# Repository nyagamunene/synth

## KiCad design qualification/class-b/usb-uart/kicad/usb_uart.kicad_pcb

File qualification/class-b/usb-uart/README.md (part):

# USB-C dual UART + RS-485 adapter (SYN-66)

Status: design, placement and a FreeRouting route that passes Synth's release gate. The routed PCB, KiCad project and reports are in this PR. Not fabricated, not tested on hardware.
Do not call it proven or clean. The list of what is unchecked is at the bottom.

Intended use: bench or lab adapter, short cables, point-to-point or last node on an RS-485 bus. Not for industrial installs, long cable runs or a node in the middle of a multidrop bus: A and B have no surge protection beyond the transceiver's built-in ESD, and the 120 ohm termination is always connected. The surge parts and a selectable termination are a later revision; the registry parts for them are in #356.

## What it is

- One USB-C port, one WCH CH342F (two UARTs).
- UART1 goes to pin headers as TTL (J2: GND, TXD1, RXD1; J3: DTR1, RTS1, CTS1).
- UART0 drives a TI THVD1450D RS-485 transceiver. Header J4: A, B, GND.
- DTR0/TNOW0 switches the transceiver direction. R_TNOW (4.7k to GND) puts UART0 in the CH342 half-duplex mode.
- Protection: PRTR5V0U2X on D+/D-, PTVS6V0S1UR on VBUS, CC1 and CC2. A 3.3 V LDO (LP5907) feeds the +3V3 rail.
- Four M2.5 mounting holes (H1 to H4), pinned in the placement sidecar: two at the top corners, two on the left and right edges at mid-height. The bottom corners are taken by the header row. Screw size and standoff height are not chosen.
- Source: `usb_uart.synth`. Sidecar: `usb_uart.placement.layout.toml` (board mm). The schematic has no sidecar: the compiler lays it out, one region per group.

## VIO jumper (J_VIO)

VIO is the I/O rail of both UARTs, the reset pin and the RS-485 chip. It is always 3.3 V or 5 V.
The THVD1450 needs 3 V or more, so 1.8 V and target-powered VIO were dropped.

| Jumper | VIO | Notes |
| --- | --- | --- |
| pins 1-2 | 3.3 V (LP5907) | default choice |
| pins 2-3 | 5 V (VBUS) | |
| none | off | CH342F stays in reset (VIO under 0.8 to 1.15 V), no enumeration. VIO LED is off. |

- VIO is not on J2 or J3, so a target cannot back-feed it. Do not wire anything to J_VIO pin 2.
- Forgotten jumper: the board only looks dead, and the VIO LED shows it.
- Not harmless with a powered target: a target driving RXD1 or CTS1 with VIO off goes past the CH342F limit of VIO+0.5 V.
  R5 and R6 (1k) limit the current to about 2.6 mA (3.3 V target) or 4.3 mA (5 V). The datasheet gives no clamp rating. Add the jumper first.

## Unused CH342F pins

- RI0, RI1, DCD0, DCD1, DSR0, DSR1: R8 (10k) pulls them to VIO (inactive, active low).
- CTS0: R9 (10k) holds it low, so UART0 flow control cannot stall.
- RST: left open (internal pull-up). The datasheet says unused lines may be left open; they are tied anyway.
- CTS1 floats if J3 is unplugged. Datasheet gives no pull-up for it.
- Datasheet 5.3: a pull-down on DTR1 at power-on switches UART1 to half-duplex. A target that holds DTR1 low at power-up changes the mode.

## BOM

| Ref | Part | MPN | Datasheet (revision seen) |
| --- | --- | --- | --- |
| U1 | WCH USB dual UART | CH342F | https://www.wch-ic.com/downloads/CH342DS1_PDF.html, V1E (file id 295, dated 2022-01-27) |
| U3 | TI RS-485 transceiver | THVD1450D | https://www.ti.com/lit/ds/symlink/thvd1450.pdf, SLLSEY3E (May 2018, rev May 2019) |
| U2 | TI 3.3 V LDO | LP5907MFX-3.3 | https://www.ti.com/lit/ds/symlink/lp5907.pdf, SNVS798Q (rev Jul 2025) |
| D1 | Nexperia USB ESD | PRTR5V0U2X | https://assets.nexperia.com/documents/data-sheet/PRTR5V0U2X.pdf, dated 1 Apr 2023 |
| D2, D5, D6 | Nexperia TVS 6 V | PTVS6V0S1UR | https://assets.nexperia.com/documents/data-sheet/PTVSXS1UR_SER.pdf, dated 1 Dec 2025 |
| D3 | Lite-On green LED | LTST-C190KGKT | https://optoelectronics.liteon.com/upload/download/DS22-2000-074/LTST-C190KGKT.PDF, revision not checked (site not reachable) |
| D4, D7 | Lite-On red LED | LTST-C190KRKT | https://optoelectronics.liteon.com/upload/download/DS-22-99-0151/LTST-C190KRKT.PDF, revision not checked (site not reachable) |
| J1 | USB-C receptacle | TYPE-C-31-M-12 | none in the registry, not checked |
| J2, J3, J4, J_VIO | 2.54 mm headers | generic 1x3 | none |
| C2, C3 | 2.2 uF X7R 0603 | generic | none |
| C4, C5, C6, C7 | 100 nF X7R 0603 | generic | none |
| R1, R2 | 5.1k | generic | none |
| R3, R4, R7 | 470 | generic | none |
| R5, R6 | 1k | generic | none |
| R8, R9 | 10k | generic | none |
| R_TNOW | 4.7k 1% | generic | none |
| R_TERM | 120 ohm 1% | generic | none |

Checked by me against the manufacturer file in this work: CH342F, THVD1450D, LP5907 (revision line only), the two Nexperia parts (revision line only).
The Nexperia and LP5907 electrical numbers were not re-read.

## Placement and routing (this commit)

Status: compact placement done and routed with FreeRouting. The route passes Synth's release gate; it is not reviewed or fabricated.

- Two copper layers: signals on F.Cu and B.Cu, a GND pour on both. The route uses no inner layer because the board has none; the previous revision was four layers with two inner GND planes that carried no routing.
- Outline: 40.99 x 32.23 mm as routed. The four M2.5 holes are at x 5.5 and 39.6 mm, y 3.0 and 21.0 mm, with a 2.2 mm board-feature rim. The header courtyards at y 29.9 mm set the 32.23 mm height. This is 3.5 mm shorter than the previous 35.73 mm compact layout and 7.5 mm shorter than the 39.73 mm committed board.
- Board-feature rim: Synth gives a mounting hole, test point or fiducial a fixed 2.2 mm rim in the fitted outline. With this sidecar the rim does not decide the outline: the holes are not the outermost parts, and the export gives the same outline with the rim set to 0. It matters if a hole is moved to the edge, where the tight 1.5 mm fit would otherwise cut it and split the F.Cu GND pour. `tests/usb_uart_board.rs` checks that every hole keeps at least 1.5 mm of room to Edge.Cuts on the exported board. The exporter sets `island_removal_mode 0`, dropping copper islands that touch no pad. KiCad lists a GND zone against itself when two fill islands that reach pads are not joined; Synth's gate now blocks on that. The previous revision had exactly this split.
- Every part has a position in `usb_uart.placement.layout.toml`. J1 sits flush on the top edge. J_VIO, J2, J3 and J4 sit at y 29.9 mm. J_VIO, J2, J3 and J4 are at x 7.36, 16.46, 26.0 and 35.1 mm. J3 and J4 each moved 1 mm left of their previous 27.0 and 36.1 mm: at the previous spot the GND pour split into two islands (C4 pin 2, J2 pin 1, D3 pin 1 and one via were cut off) and, with current KiCad and FreeRouting here, DTR1 was left unrouted. The 9.1 mm spacing between J3 and J4 keeps their 8.62 mm courtyards apart. The bottom parts sit at y 23.6 and 25.8 mm. R1 and R2 use the top corners; R3 moved to x 14.5 mm to clear H3.
- No courtyard overlaps. J1 courtyard to top edge: 0.01 mm. That is the 0.5 mm courtyard margin reaching the edge: the shell front face sits 0.50 mm inside Edge.Cuts. The HRO drawing states no overhang limit, so only the enclosure cutout fit is left to check.
- Pad-edge gap to the target pad on the same net:

| Part | Target | Gap mm |
| --- | --- | --- |
| C4 (VDD5) | U1 pin 7 | 0.97 |
| C5 (V3) | U1 pin 6 | 1.14 |
| C6 (VIO) | U1 pin 5 | 0.99 |
| C7 (VCC) | U3 pin 8 | 0.99 |
| C2 (LDO in) | U2 VBUS pins | 0.99 |
| C3 (LDO out) | U2 pin 5 | 0.99 |
| D1 D+ / D- | J1 D+ / D- pads | 1.76 / 1.69 |
| D2 (VBUS TVS) | J1 VBUS pad | 2.34 |
| D5 (CC1 TVS) | J1 CC1 pad | 1.95 |
| D6 (CC2 TVS) | J1 CC2 pad | 1.60 |

- D2 is over 2 mm: four protection parts do not fit side by side under the 7 mm of J1 pads any closer.
- R1 and R2 are in the top corners; the remaining passives are placed by hand. The DRC checks their courtyards, not placement quality.

Routing (FreeRouting 2.4.1, `router: "freerouting"`, `allow_via_in_pad: true`), with the Synth sources at `08b917b` (`source_revision` in `reports/release.json`):
- Result: routed. `release.json` has `release_ready` true and `routing.state` "routed", with no open net. `kicad-cli pcb drc --severity-all --refill-zones`: 0 errors, 0 warnings and no `unconnected_items`. Synth's gate no longer accepts a GND zone that KiCad lists against itself, and the delivered board has none. pcbnew's connectivity puts every GND pad and via in one cluster, so the pour is connected. (The earlier revision's 36 library-link warnings came from a run without the KiCad libraries.)
- 273 track segments, 43 vias, 515.4 mm of copper.
- The routed board is 40.99 x 32.23 mm.
- FreeRouting's escape analysis flags J1 and U1 (0.5 mm pitch) as the packages where neither a fabrication-floor via nor a minimum track fits between adjacent pads, and suggests 4 layers. The route still completes, with its only via-in-pad at U1 pin 25.
- J3 is at x 26.0 mm and J4 at x 35.1 mm in the sidecar. Small placement changes change FreeRouting's result: shifts of 0.5 mm in J3 and J4 left DTR1, TNOW0 or +3V3 unrouted, and a 0.5 mm shift of C4 left USB_DN open. The same inputs gave the same board on three runs.
- Via-in-pad at the U1 exposed pad (pin 25), at (23.900, 17.300) mm. The fab must fill and cap it. JLCPCB has not been asked.
- Signal-integrity pass: 23 warnings, none blocking. All 23 are layer changes with no ground return via within 1.53 mm, so the return current has to jump between the F.Cu and B.Cu pours.
- The USB pair is not coupled. Measured on the committed board: full-speed part, pair on F.Cu only with no via (the 23 layer-change warnings are on other nets), DP 38.63 mm and DN 13.52 mm so 25.11 mm of skew (about 0.2 percent of a full-speed bit), and 91.4 percent of the length over solid B.Cu GND fill. These are my measurements, not an independent review; see `qualification.json`. FreeRouting does not couple the pair. On two layers at 1.6 mm, a 90 ohm differential pair needs about 1.18 mm traces, so the pair has no impedance target and no controlled-impedance geometry (the previous four-layer revision declared 90 ohm but never verified it).
- No part has been reviewed (`reviewer_state` is false for every part in `release.json`).
- Silkscreen: the D7, J4, J_VIO and U1 reference labels are placed by hand in the sidecar. `kicad-cli pcb drc` reports no silkscreen warning.
- TX LEDs: D4 and D7 take their current from VIO through R4 and R7 and sink it into TXD0 and TXD1, so they are dark while a line idles and lit on the low bits. Each draws about 3 mA at 3.3 V and 6.6 mA at 5 V from the CH342 TXD pin (an estimate from a 1.9 V forward drop; the CH342 output drive was not checked at 5 V).

## Committed artifacts

- `kicad/`: the routed PCB, schematic, symbol library, project, DRC rules and BOM.
- `reports/`: `release.json`, the delivered DRC, ERC and the routing record. Its `production_status` and `release_ready` fields only mean the route passed Synth's router and DRC gates, and its `gate_scope` field says so. Neither is a fabrication approval.
- `qualification.json`: the qualification gate. `qualified` stays false until every review gate in it is true.
- `dfm/`: the gerber zip, CPL and screenshots from the JLCPCB quote and DFM flow on 2026-10-27 (no order placed). It is partial: see `jlcpcb_dfm` in `qualification.json`.
- `images/`: 3D top and angled, top and bottom copper, and the schematic. The 3D and copper pictures were rendered with `kicad-cli pcb render` and `pcb export pdf` from the committed board.
- `dfm/`: regenerated Gerbers, drill and CPL for this board. The JLCPCB screenshots there are from the previous revision and were not redone; see `qualification.json`.
- `SHA256SUMS`: hashes of the artifacts above.

The reports are as the commands produce them, except that the absolute paths of the machine that produced them were cut to repo-relative ones (`out/...` is the export directory) and `source_revision` in `reports/release.json` was added by hand. The release report is the CLI's own format (`synth.release.v1`), which differs from the MCP report in the earlier revision.

The committed board came from the CLI commands below (FreeRouting engine, via-in-pad allowed).

## Commands (use an empty `XDG_DATA_HOME` so a user registry cannot shadow parts)

```
export XDG_DATA_HOME=$(mktemp -d)
scripts/setup-routing-engines.sh --freerouting-only
synth validate qualification/class-b/usb-uart/usb_uart.synth
synth export-kicad qualification/class-b/usb-uart/usb_uart.synth --out /tmp/usb_uart --router free-routing --krt-allow-via-in-pad
kicad-cli pcb drc --severity-all --refill-zones --format json /tmp/usb_uart/usb_uart.kicad_pcb -o /tmp/usb_uart/usb_uart-drc.json
kicad-cli sch erc --severity-all --format json /tmp/usb_uart/usb_uart.kicad_sch -o /tmp/usb_uart/usb_uart-erc.json
(cd qualification/class-b/usb-uart && sha256sum -c SHA256SUMS)
```

A route that passes the gate is `usb_uart.kicad_pcb`; a failed one stays in `usb_uart.freerouting.kicad_pcb`. The unrouted placement is `usb_uart.synth.kicad_pcb`.
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
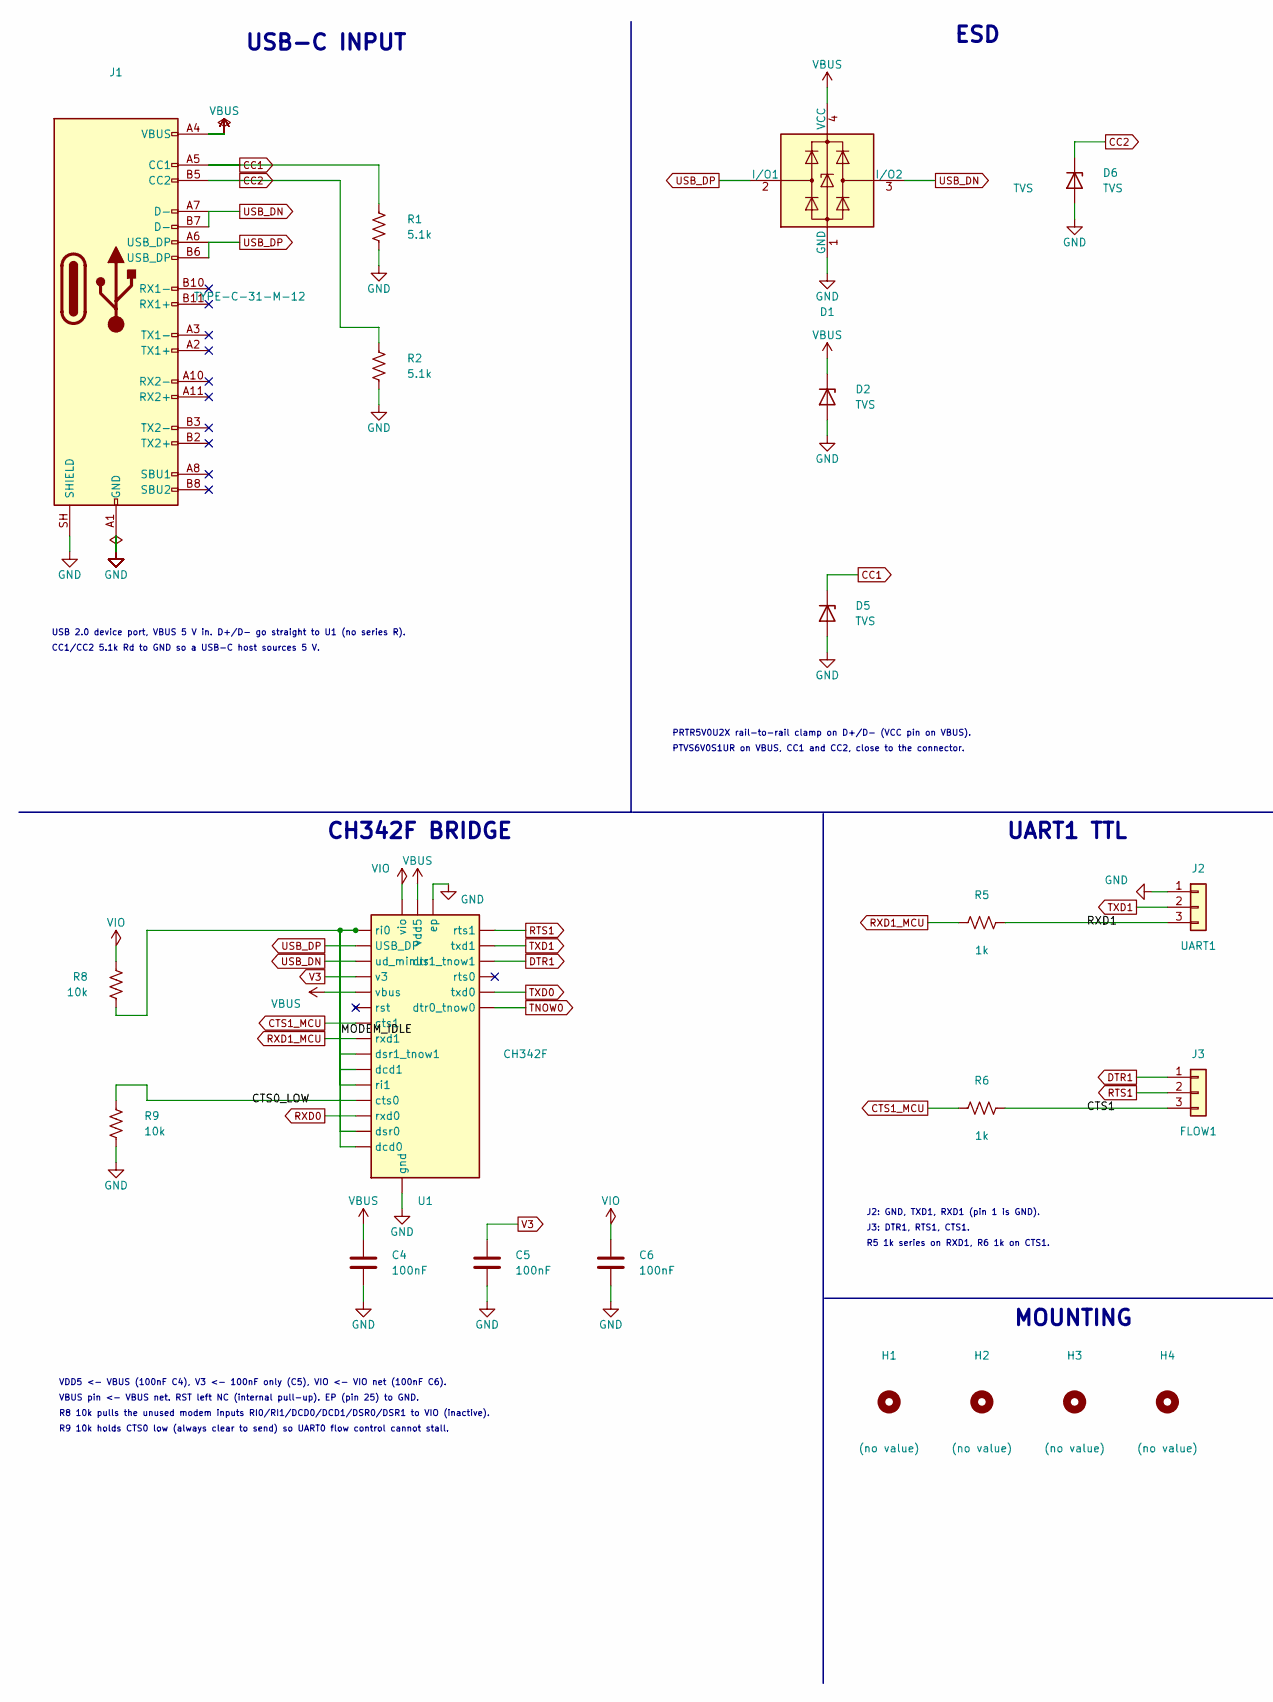
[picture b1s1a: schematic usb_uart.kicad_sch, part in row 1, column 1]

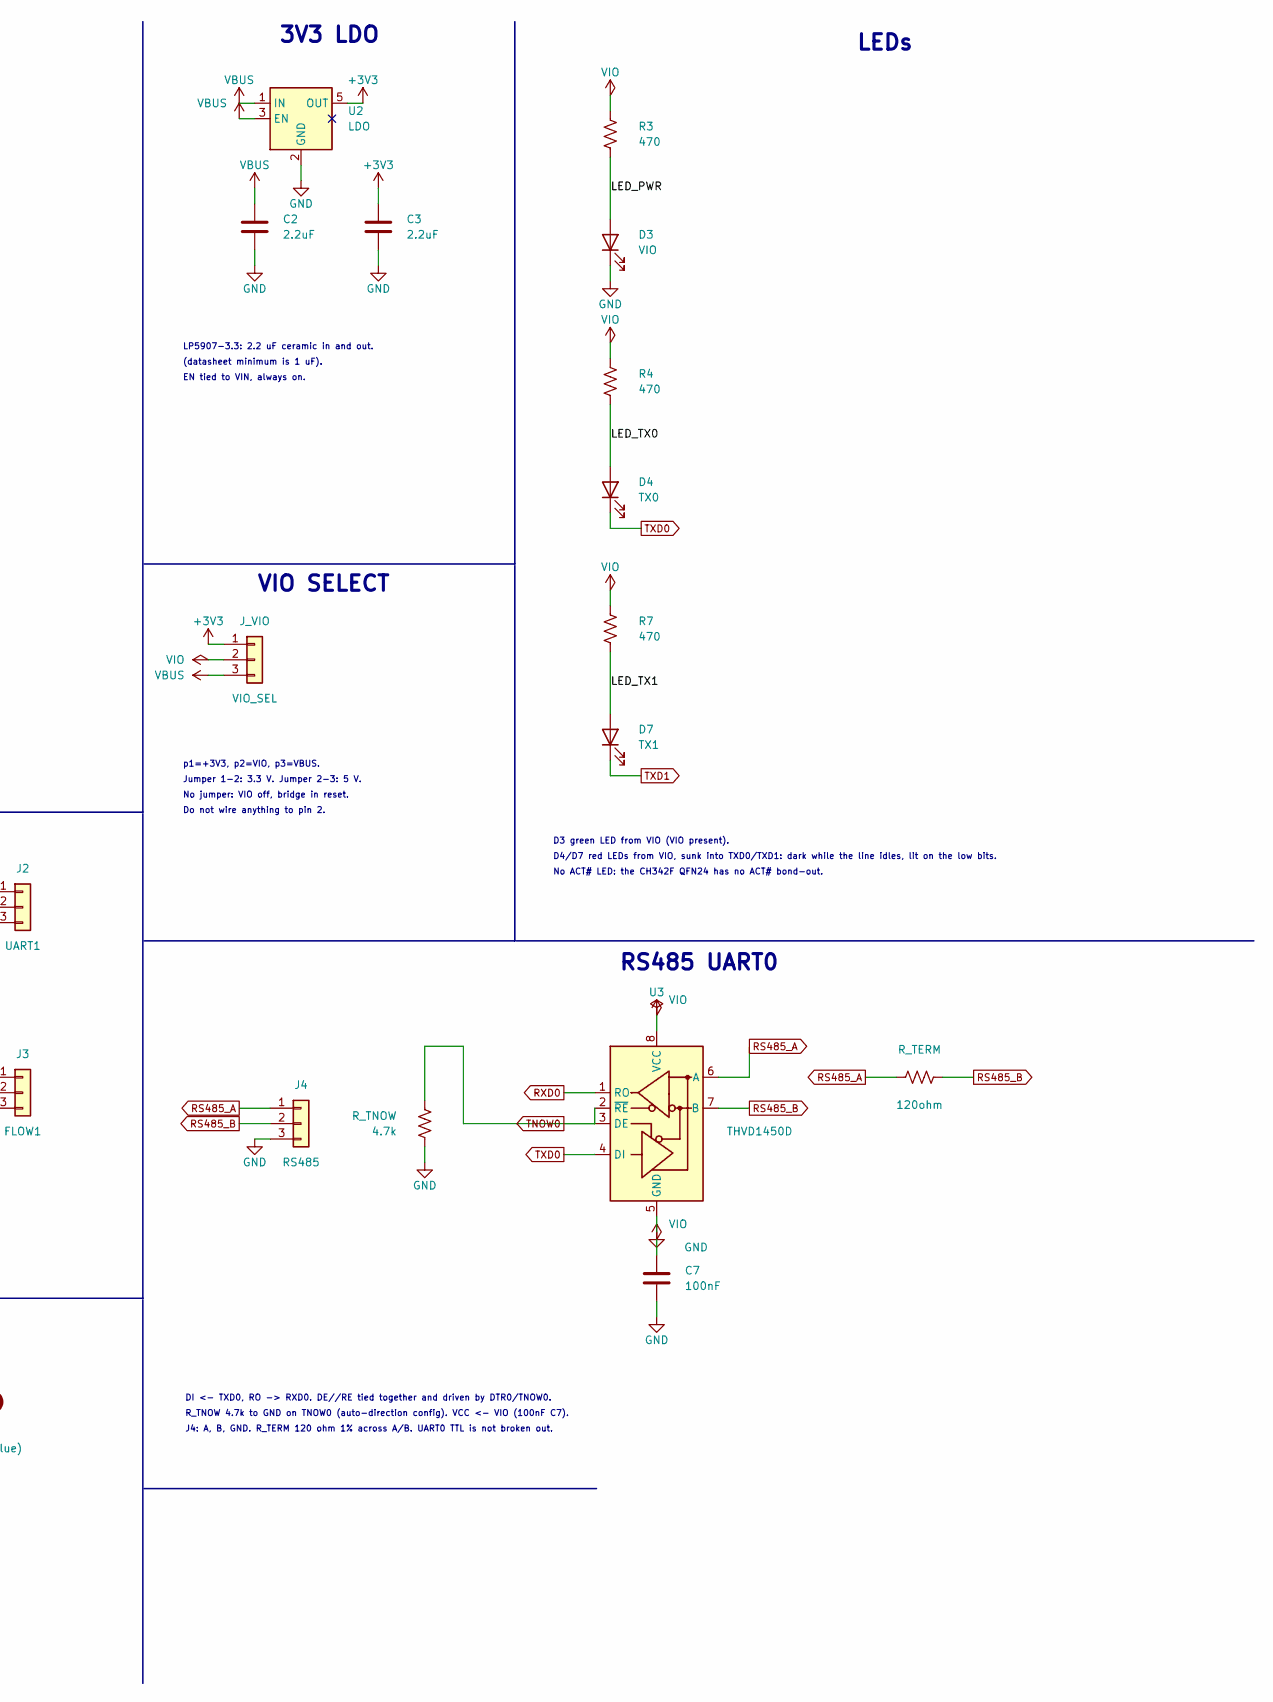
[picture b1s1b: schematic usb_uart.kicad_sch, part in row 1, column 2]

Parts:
C2, C3: 2.2uF; C_0603_1608Metric; Voltage 16V
C4, C5, C6, C7: 100nF; C_0603_1608Metric; Voltage 16V
D1: TVS; SOT-143; MPN PRTR5V0U2X
D2, D5, D6: TVS; Nexperia_CFP3_SOD-123W; MPN PTVS6V0S1UR
D3: VIO; LED_0603_1608Metric; MPN LTST-C190KGKT
D4: TX0; LED_0603_1608Metric; MPN LTST-C190KRKT
D7: TX1; LED_0603_1608Metric; MPN LTST-C190KRKT
H1, H2, H3, H4: (no value); MountingHole_2.5mm
J1: TYPE-C-31-M-12; USB_C_Receptacle_HRO_TYPE-C-31-M-12; MPN TYPE-C-31-M-12; LCSC C165948
J2: UART1; PinHeader_1x03_P2.54mm_Vertical
J3: FLOW1; PinHeader_1x03_P2.54mm_Vertical
J4: RS485; PinHeader_1x03_P2.54mm_Vertical
J_VIO: VIO_SEL; PinHeader_1x03_P2.54mm_Vertical
R1, R2: 5.1k; R_0603_1608Metric
R3, R4, R7: 470; R_0603_1608Metric
R5, R6: 1k; R_0603_1608Metric
R8, R9: 10k; R_0603_1608Metric
R_TERM: 120ohm; R_0603_1608Metric; Tolerance 1%
R_TNOW: 4.7k; R_0603_1608Metric; Tolerance 1%
U1: CH342F; QFN-24-1EP_4x4mm_P0.5mm_EP2.6x2.6mm; MPN CH342F; LCSC C2841530
U2: LDO; SOT-23-5; MPN LP5907MFX-3.3; LCSC C83437
U3: THVD1450D; SOIC-8_3.9x4.9mm_P1.27mm; MPN THVD1450D; LCSC C2671361

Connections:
+3V3: C3.1, J_VIO.1, U2.5 (OUT)
CC1: D5.1 (K), J1.A5 (CC1), R1.1
CC2: D6.1 (K), J1.B5 (CC2), R2.1
CTS0_LOW: R9.1, U1.18 (cts0)
CTS1: J3.3, R6.2
CTS1_MCU: R6.1, U1.10 (cts1)
DTR1: J3.1, U1.15 (dtr1_tnow1)
GND: C2.2, C3.2, C4.2, C5.2, C6.2, C7.2, D1.1 (GND), D2.2 (A), D3.1 (K), D5.2 (A), D6.2 (A), J1.A1 (GND), J1.A12 (GND), J1.B1 (GND), J1.B12 (GND), J1.SH (SHIELD), J2.1, J4.3, R1.2, R2.2, R9.2, R_TNOW.2, U1.2 (gnd), U1.25 (ep), U2.2 (GND), U3.5 (GND)
LED_PWR: D3.2 (A), R3.2
LED_TX0: D4.2 (A), R4.2
LED_TX1: D7.2 (A), R7.2
MODEM_IDLE: R8.2, U1.1 (ri0), U1.14 (dsr1_tnow1), U1.16 (dcd1), U1.17 (ri1), U1.22 (dsr0), U1.24 (dcd0)
RS485_A: J4.1, R_TERM.1, U3.6 (A)
RS485_B: J4.2, R_TERM.2, U3.7 (B)
RTS1: J3.2, U1.11 (rts1)
RXD0: U1.20 (rxd0), U3.1 (RO)
RXD1: J2.3, R5.2
RXD1_MCU: R5.1, U1.12 (rxd1)
TNOW0: R_TNOW.1, U1.23 (dtr0_tnow0), U3.2 (~RE), U3.3 (DE)
TXD0: D4.1 (K), U1.21 (txd0), U3.4 (DI)
TXD1: D7.1 (K), J2.2, U1.13 (txd1)
USB_DN: D1.3 (I/O2), J1.A7 (D-), J1.B7 (D-), U1.4 (ud_minus)
USB_DP: D1.2 (I/O1), J1.A6 (D+), J1.B6 (D+), U1.3 (ud_plus)
V3: C5.1, U1.6 (v3)
VBUS: C2.1, C4.1, D1.4 (VCC), D2.1 (K), J1.A4 (VBUS), J1.A9 (VBUS), J1.B4 (VBUS), J1.B9 (VBUS), J_VIO.3, U1.7 (vdd5), U1.8 (vbus), U2.1 (IN), U2.3 (EN)
VIO: C6.1, C7.1, J_VIO.2, R3.1, R4.1, R7.1, R8.1, U1.5 (vio), U3.8 (VCC)

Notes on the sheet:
MOUNTING
USB-C INPUT
ESD
3V3 LDO
CH342F BRIDGE
VIO SELECT
UART1 TTL
RS485 UART0
LEDs
USB 2.0 device port, VBUS 5 V in. D+/D- go straight to U1 (no series R).
CC1/CC2 5.1k Rd to GND so a USB-C host sources 5 V.
PRTR5V0U2X rail-to-rail clamp on D+/D- (VCC pin on VBUS).
PTVS6V0S1UR on VBUS, CC1 and CC2, close to the connector.
LP5907-3.3: 2.2 uF ceramic in and out.
(datasheet minimum is 1 uF).
EN tied to VIN, always on.
VDD5 <- VBUS (100nF C4), V3 <- 100nF only (C5), VIO <- VIO net (100nF C6).
VBUS pin <- VBUS net. RST left NC (internal pull-up). EP (pin 25) to GND.
R8 10k pulls the unused modem inputs RI0/RI1/DCD0/DCD1/DSR0/DSR1 to VIO (inactive).
R9 10k holds CTS0 low (always clear to send) so UART0 flow control cannot stall.
p1=+3V3, p2=VIO, p3=VBUS.
Jumper 1-2: 3.3 V. Jumper 2-3: 5 V.
No jumper: VIO off, bridge in reset.
Do not wire anything to pin 2.
J2: GND, TXD1, RXD1 (pin 1 is GND).
J3: DTR1, RTS1, CTS1.
R5 1k series on RXD1, R6 1k on CTS1.
DI <- TXD0, RO -> RXD0. DE//RE tied together and driven by DTR0/TNOW0.
R_TNOW 4.7k to GND on TNOW0 (auto-direction config). VCC <- VIO (100nF C7).
J4: A, B, GND. R_TERM 120 ohm 1% across A/B. UART0 TTL is not broken out.
D3 green LED from VIO (VIO present).
D4/D7 red LEDs from VIO, sunk into TXD0/TXD1: dark while the line idles, lit on the low bits.
No ACT# LED: the CH342F QFN24 has no ACT# bond-out.

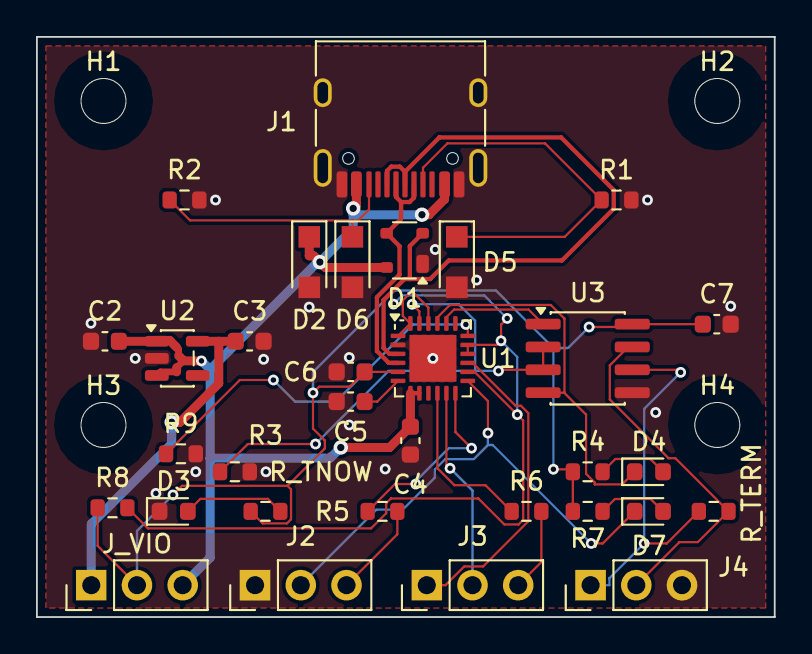
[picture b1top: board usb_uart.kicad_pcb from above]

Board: 2 copper layers, 41.0 x 32.2 mm, 36 parts (0 on the bottom side), 26 nets.

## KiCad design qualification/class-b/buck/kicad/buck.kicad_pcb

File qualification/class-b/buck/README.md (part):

# 24 V in, 3.3 V out buck with input parts (PTC, reverse-block diode, TVS) (SYN-67)

Status: designed, placed by a hand-pinned sidecar, routed, DRC and ERC counted, Gerber and drill files
generated. Not fabricated, not powered, no hardware test. Two parts on the board have no reviewer
(`lmr38010`, `ltst_c190kgkt`), so the fab package reports `release_ready: false` by design. The review
evidence for both is below and is a draft for the maintainer, not a sign-off.
Intended for 24 V +10% in and 1 A out. The converter is rated 1 A, and the PTC and the input connector are
further limits (see Limits). No surge test was run. The TVS clamp (48.4 V at 12.4 A) is below the
converter's 85 V absolute maximum; a sustained overvoltage is limited by the PTC and the 50 V capacitors.

## Purpose

Ticket #67 under #38 (Class B qualification): a switching-regulator board with input and output filtering,
feedback, power-good and thermal copper, plus a negative variant that the feedback-safety rule
(E-SYNTH-POWER-011, PR #56) must flag.

## What

- `buck.synth`, negative `buck_neg_fb_sw.synth`, the placement sidecar `buck.placement.layout.toml`, hashes in `SHA256SUMS`, matrix and `#38` traceability in `QUALIFICATION.md`, evidence in `kicad/`, `reports/`, `images/`.
- `kicad/`: the KiCad project, BOM, pick-and-place, `gerbers/` (22 Gerbers plus the job file, 4 copper layers) and `drill/` (PTH and NPTH). `reports/`: `release.json` (source/DRC gate) and `release-fab.json` (fab package, untrusted), DRC, ERC, routing and connectivity.
- Chain: J1 (JST XH) -> F1 PTC -> D1 SS36 Schottky (reverse block) -> VIN node.
  VIN node: D2 SMBJ30A TVS, C1 47 uF bulk, C2 10 uF, C3 220 nF (on the U1 VIN pin), U1 LMR38010, UVLO divider.
- U1 -> L1 6.8 uH -> C5, C6, C9 (3x 22 uF, 25 V X7R) -> J2. C4 100 nF boot. R_RT 33k from RT/SYNC to GND sets 800 kHz. U1 has no VCC pin, so there is no VCC capacitor.
- U1 pins: 1 GND, 2 EN, 3 VIN, 4 RT/SYNC, 5 FB, 6 PG, 7 BOOT, 8 SW, 9 exposed pad.
- Feedback: R_FB_T 100k from the output node (L1 pad 2 side), R_FB_B 43.2k, C7 56 pF across R_FB_T.
  Vout = 1.0 x (1 + 100k/43.2k) = 3.315 V typical, 3.26 to 3.36 V over Vref 0.985 to 1.015 V (ideal resistors).
- Power-good: U1 pin 6 is open drain, pulled up to +3V3 through R_PG 100k and brought out on J2 pin 3. D4 (green, "PG FAULT") and R_PGLED 470 R run from +3V3 to PG, so the LED lights while PG is low and stays dark while power is good.
- Thermal: U1 pin 9 is a 2.41 x 3.1 mm exposed pad soldered to the F.Cu GND pour, with a 2 x 3 array of six GND vias in the pad (see Thermal). The board is `manufacturer "jlc-filled-via"` with `requires via_in_pad` (resin-filled and capped vias).
- Negative file: identical except R_FB_T and C7 hang from SW. It emits E-SYNTH-POWER-011 and the same 14 warnings as the good board.
- Board: 70.99 x 33.99 mm (2413 mm2, Edge.Cuts line centres), 4 layers, GND pours on all layers. Power tracks 0.5 mm, signal 0.127 mm.
- Two M2.5 non-plated mounting holes (H1, H2) in opposite corners.

## Why LMR38010 and not LMR33640

The first revision used the LMR33640 (38 V absolute maximum). A review found that the SMBJ30A clamps at 48.4 V
(12.4 A), above that maximum, so the TVS could not protect it. The LMR38010 is rated 85 V absolute maximum
(SW 85 V too), above the clamp. The change also removed the VCC pin and its capacitor, moved PG to pin 6
and VIN to pin 3, and added R_RT.

## UVLO (LMR38010 SNVSBM3B, 9.2.2.8, Eq 13 and 14)

Datasheet values: VEN-H (rising) 1.1 / 1.25 / 1.4 V and VEN-L (falling) 0.95 / 1.10 / 1.22 V (min/typ/max).
R_UV_B = 100k, R_UV_T = 1.37M, ratio 1 + 13.7 = 14.7.
- Start = 1.25 x 14.7 = 18.4 V typical (16.2 to 20.6 V over the VEN-H range).
- Stop = 1.10 x 14.7 = 16.2 V typical (14.0 to 17.9 V over the VEN-L range).
- The min and max of the two ranges are not independent, so the extreme pairs are not a guaranteed hysteresis. 1% resistors add about 1% to each figure.
- EN at 28 V in is 28 x 0.1/1.47 = 1.90 V; the EN absolute maximum is VIN + 0.3 V.

## Frequency and inductor

- R_RT 33k gives 800 kHz (datasheet RT versus frequency table under Figure 8-4; Table 8-1 lists 750 kHz at 34.8k and 1000 kHz at 25.5k). The RT/SYNC pin must not float (8.3.4).
- L1 6.8 uH: ripple (26.4 - 3.3) x (3.3/26.4) / (6.8 uH x 800 kHz) = 0.53 A pp at 26.4 V in. Eq 11 minimum is 0.25 x 3.3 / 800 kHz = 1.03 uH. At 1 A out the peak is about 1.27 A against Isat 5.7 A.
- Datasheet Table 9-1 has no 3.3 V row. Its 5 V rows use 2 to 3 x 22 uF; C5, C6 and C9 are 3 x 22 uF at 25 V X7R. DC-bias derating at 3.3 V is unknown and stability is unverified.

## Power-good

| Item | Value | Source |
| --- | --- | --- |
| Pin | U1 pin 6, open-drain NMOS | SNVSBM3B 8.3.5 |
| Pull-up | R_PG 100k to +3V3 | 8.3.5 allows a 100k pull-up to VOUT; the pin tolerates 20 V (7.1, 7.3) |
| Sink current | 33 uA through 100k, limit 5 mA DC | 8.3.5 |
| On-resistance | 92 ohm typ at VEN 3.3 V, 140 ohm at VEN 0 | 7.5 |
| Asserted low | during start-up, current limit and thermal shutdown, and when EN is low | 8.3.5 |
| Thresholds | rising 110 / 112 / 114 %, falling 90 / 92 / 94 % of VFB, hysteresis 2.2 % | 7.5 |
| Start-up delay | about 4 ms from EN asserted | 8.3.5 |
| Glitch filter | 40 us typ | 7.5 |
| Presented on | J2 pin 3 (3.3 V logic) | this board |

The netlist proves the connection (A15 in `QUALIFICATION.md`). Nothing proves the thresholds, the delay or
the behaviour on a fault: Synth has no power-good rule (`synth capability list` marks
`power_sequencing_and_power_good` unsupported), and this board was not powered.

## Thermal

- U1's exposed pad (pin 9, 2.41 x 3.1 mm, centre (33.0, 16.0) mm) is soldered to the F.Cu GND pour and holds
  a 2 x 3 array of six GND vias (0.6 mm pad, 0.3 mm drill, 1.2 mm apart), declared in
  `buck.placement.layout.toml` as `[[vias]]`. The PCB export writes them before routing, so the router
  treats them as GND copper. TI asks for at least a 4 x 3 array of 10 mil vias (9.5.1.1); six vias is fewer.
- Via-in-pad needs resin-filled and capped vias, so the board declares `manufacturer "jlc-filled-via"` and
  `requires via_in_pad`; `release.json` lists the six vias as fabrication notes.
- Counts from `kicad/buck.kicad_pcb` (`vias.py`, GND vias, distance from the pad centre): inside the pad 6;
  within 1 mm 2, within 2 mm 6, within 3 mm 6, within 4 mm 7. The board has 21 vias in total, all GND, all
  0.3 mm drill and 0.6 mm pad. The other 15 were placed by the router.
- Not estimated: TI's `RthetaJA` of 42.9 C/W is not valid for design (datasheet text near Eq 15), the LMR38010
  datasheet has no copper-area curve, and no efficiency curve was read. At 1 A out and an assumed 85% efficiency the loss
  would be 3.3/0.85 - 3.3 = 0.58 W; the junction temperature is left to the expert (B2).

## Parts and datasheets (read 2026-10-24 and 2026-10-29)

| Part | Datasheet | Revision | Values taken | Conflict or gap |
| --- | --- | --- | --- | --- |
| U1 TI LMR38010SDDAR (HSOIC-8 DDA) | https://www.ti.com/lit/ds/symlink/lmr38010.pdf | SNVSBM3B | 4.2-80 V recommended, 85 V abs max (SW 85 V); 1 A; 200-2200 kHz adjustable; internal compensation; VREF 1.0 V (0.985-1.015); EN rising 1.1/1.25/1.4 V, falling 0.95/1.10/1.22 V; PG tolerates 20 V; pins 1 GND, 2 EN, 3 VIN, 4 RT/SYNC, 5 FB, 6 PG, 7 BOOT, 8 SW, 9 EP; Cin at least 4.7 uF plus 100-220 nF (9.2.2.6) | Table 8-1 has no 800 kHz row; the RT table under Figure 8-4 gives 33k. Table 9-1 has no 3.3 V row |
| L1 Bourns SRN6045TA-6R8M | https://www.bourns.com/docs/Product-Datasheets/SRN6045TA.pdf | REV. 06/24 (footer) | 6.8 uH +-20%, DCR 34 mOhm typ, Irms 3.6 A, Isat 5.7 A (L -30%), 6.0 x 6.0 mm | Registry has no Isat field; Isat is in the description |
| D1 Vishay SS36 | https://www.vishay.com/docs/88751/ss32.pdf | 23-Apr-2020 (doc 88751) | VRRM 60 V, 3 A, IFSM 100 A, VF 0.75 V max at 3 A, IR 0.5 mA at 25 C and 10 mA at 100 C, SMC | Drawn with KiCad `Device:D_Schottky`; the footprint is `Diode_SMD:D_SMC`. VF at low current not read |
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
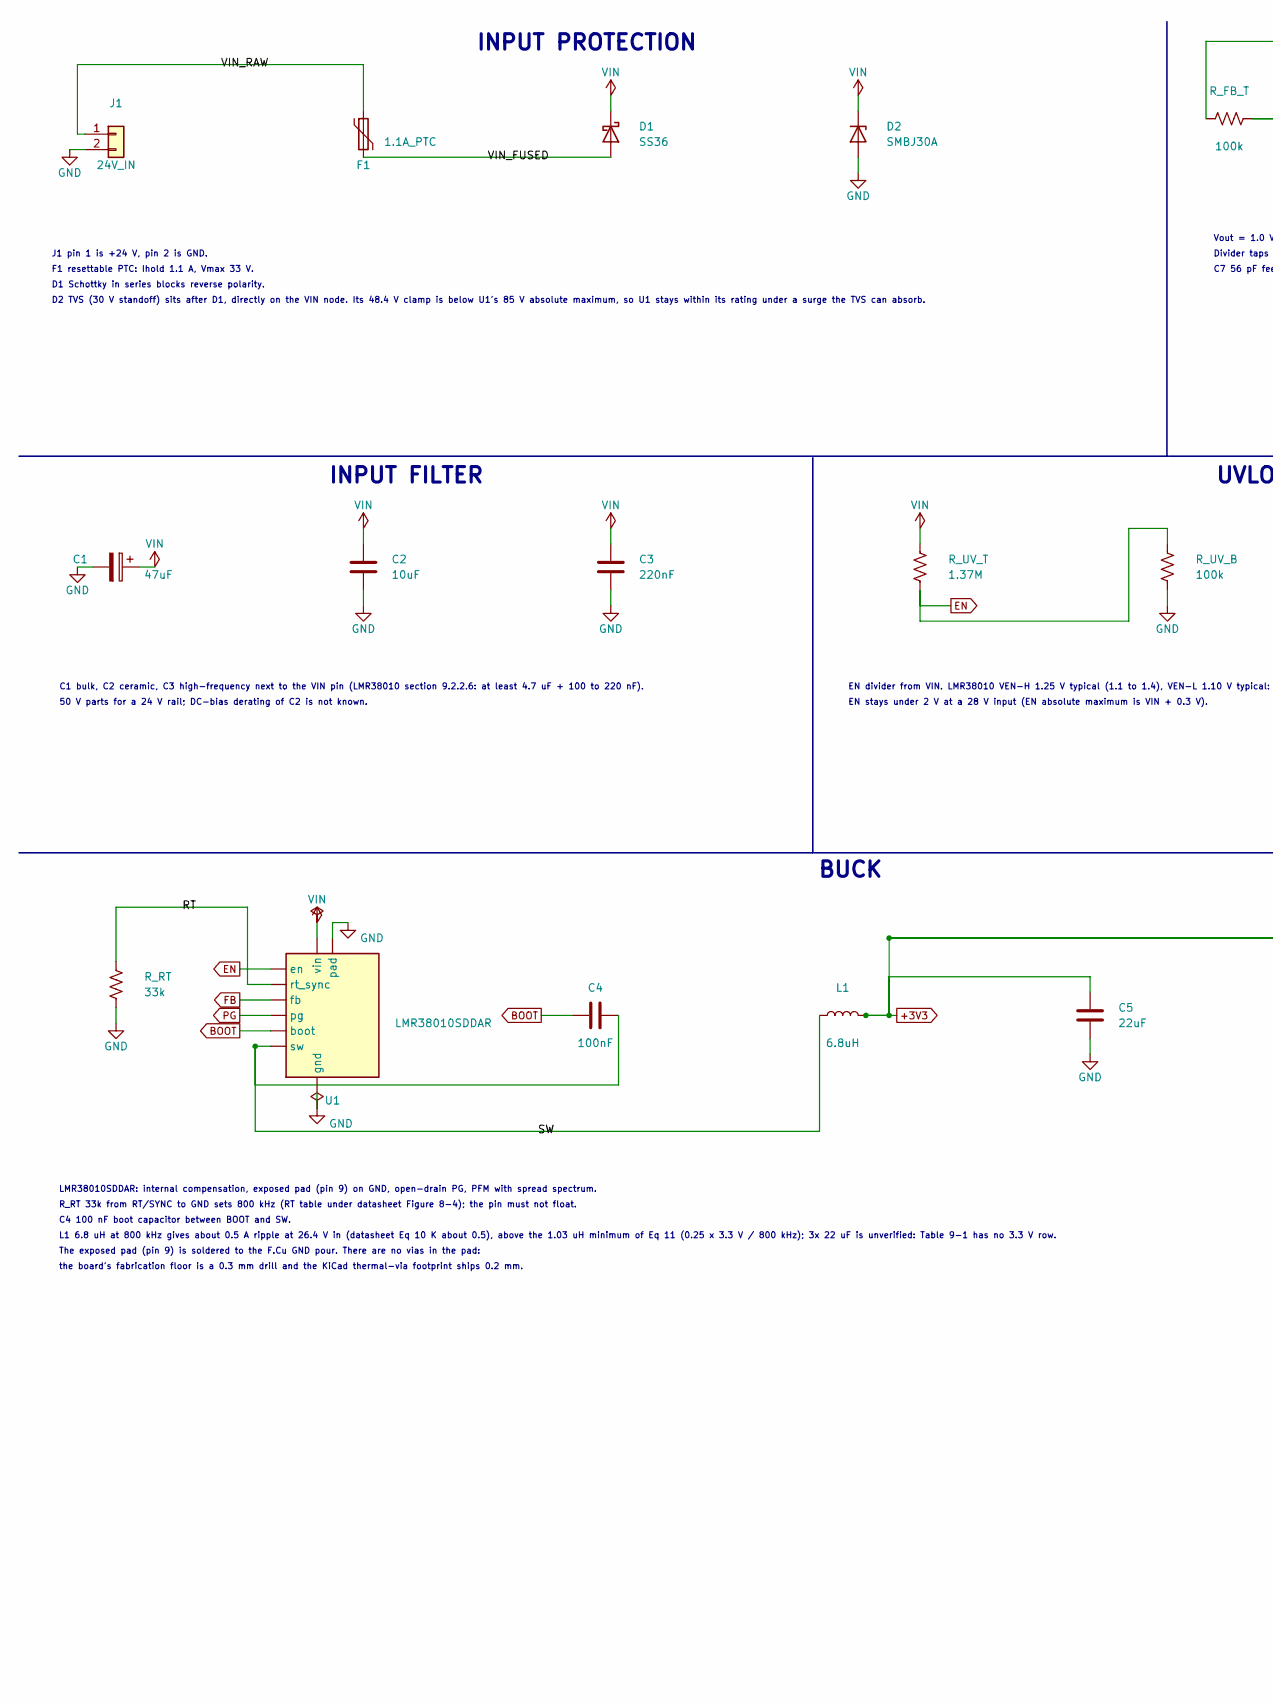
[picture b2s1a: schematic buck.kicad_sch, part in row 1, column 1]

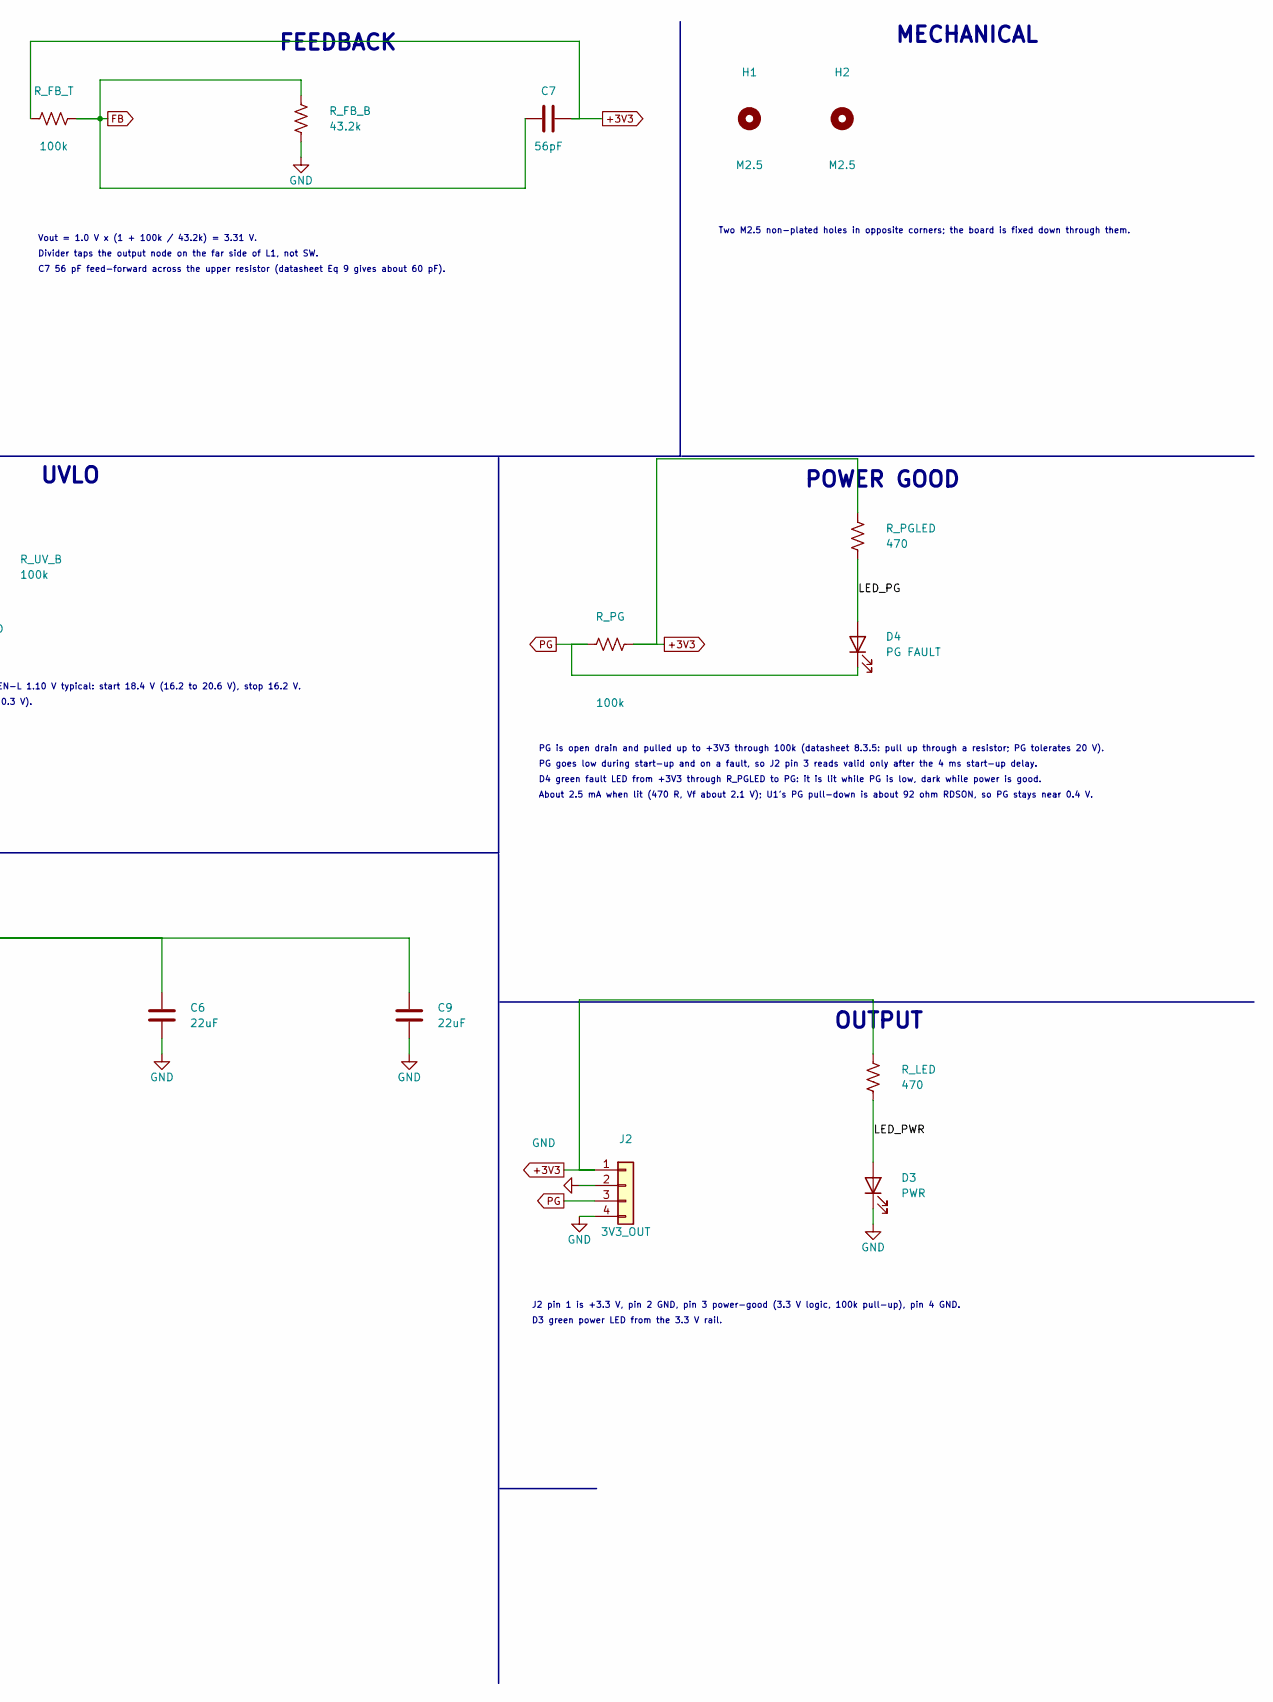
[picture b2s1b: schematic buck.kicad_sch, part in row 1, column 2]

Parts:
C1: 47uF; CP_Elec_8x10; Voltage 50V; MPN RVT1H470M0810
C2: 10uF; C_1206_3216Metric; Voltage 50V
C3: 220nF; C_0603_1608Metric; Voltage 50V
C4: 100nF; C_0603_1608Metric; Voltage 16V
C5, C6, C9: 22uF; C_1206_3216Metric; Voltage 25V
C7: 56pF; C_0603_1608Metric; Voltage 50V
D1: SS36; D_SMC; MPN SS36
D2: SMBJ30A; D_SMB; MPN SMBJ30A
D3: PWR; LED_0603_1608Metric; MPN LTST-C190KGKT
D4: PG FAULT; LED_0603_1608Metric; MPN LTST-C190KGKT
F1: 1.1A_PTC; Fuse_1812_4532Metric; MPN MF-MSMF110/33X
H1, H2: M2.5; MountingHole_2.5mm
J1: 24V_IN; JST_XH_B2B-XH-A_1x02_P2.50mm_Vertical; MPN B2B-XH-A
J2: 3V3_OUT; JST_XH_B4B-XH-A_1x04_P2.50mm_Vertical; MPN B4B-XH-A
L1: 6.8uH; L_Bourns_SRN6045TA; MPN SRN6045TA-6R8M
R_FB_B: 43.2k; R_0603_1608Metric; Tolerance 1%
R_FB_T: 100k; R_0603_1608Metric; Tolerance 1%
R_LED: 470; R_0603_1608Metric
R_PG: 100k; R_0603_1608Metric
R_PGLED: 470; R_0603_1608Metric
R_RT: 33k; R_0603_1608Metric; Tolerance 1%
R_UV_B: 100k; R_0603_1608Metric; Tolerance 1%
R_UV_T: 1.37M; R_0603_1608Metric; Tolerance 1%
U1: LMR38010SDDAR; HSOP-8-1EP_3.9x4.9mm_P1.27mm_EP2.41x3.1mm; MPN LMR38010SDDAR

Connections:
+3V3: C5.1, C6.1, C7.2, C9.1, J2.1, L1.2, R_FB_T.1, R_LED.1, R_PG.2, R_PGLED.1
BOOT: C4.1, U1.7 (boot)
EN: R_UV_B.1, R_UV_T.2, U1.2 (en)
FB: C7.1, R_FB_B.1, R_FB_T.2, U1.5 (fb)
GND: C1.2, C2.2, C3.2, C5.2, C6.2, C9.2, D2.2 (A), D3.1 (K), J1.2, J2.2, J2.4, R_FB_B.2, R_RT.2, R_UV_B.2, U1.1 (gnd), U1.9 (pad)
LED_PG: D4.2 (A), R_PGLED.2
LED_PWR: D3.2 (A), R_LED.2
PG: D4.1 (K), J2.3, R_PG.1, U1.6 (pg)
RT: R_RT.1, U1.4 (rt_sync)
SW: C4.2, L1.1, U1.8 (sw)
VIN: C1.1, C2.1, C3.1, D1.1 (K), D2.1 (K), R_UV_T.1, U1.3 (vin)
VIN_FUSED: D1.2 (A), F1.2
VIN_RAW: F1.1, J1.1

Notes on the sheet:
INPUT PROTECTION
INPUT FILTER
UVLO
BUCK
FEEDBACK
POWER GOOD
OUTPUT
MECHANICAL
J1 pin 1 is +24 V, pin 2 is GND.
F1 resettable PTC: Ihold 1.1 A, Vmax 33 V.
D1 Schottky in series blocks reverse polarity.
D2 TVS (30 V standoff) sits after D1, directly on the VIN node. Its 48.4 V clamp is below U1's 85 V absolute maximum, so U1 stays within its rating under a surge the TVS can absorb.
C1 bulk, C2 ceramic, C3 high-frequency next to the VIN pin (LMR38010 section 9.2.2.6: at least 4.7 uF + 100 to 220 nF).
50 V parts for a 24 V rail; DC-bias derating of C2 is not known.
EN divider from VIN. LMR38010 VEN-H 1.25 V typical (1.1 to 1.4), VEN-L 1.10 V typical: start 18.4 V (16.2 to 20.6 V), stop 16.2 V.
EN stays under 2 V at a 28 V input (EN absolute maximum is VIN + 0.3 V).
LMR38010SDDAR: internal compensation, exposed pad (pin 9) on GND, open-drain PG, PFM with spread spectrum.
R_RT 33k from RT/SYNC to GND sets 800 kHz (RT table under datasheet Figure 8-4); the pin must not float.
C4 100 nF boot capacitor between BOOT and SW.
L1 6.8 uH at 800 kHz gives about 0.5 A ripple at 26.4 V in (datasheet Eq 10 K about 0.5), above the 1.03 uH minimum of Eq 11 (0.25 x 3.3 V / 800 kHz); 3x 22 uF is unverified: Table 9-1 has no 3.3 V row.
The exposed pad (pin 9) is soldered to the F.Cu GND pour. There are no vias in the pad:
the board's fabrication floor is a 0.3 mm drill and the KiCad thermal-via footprint ships 0.2 mm.
Vout = 1.0 V x (1 + 100k / 43.2k) = 3.31 V.
Divider taps the output node on the far side of L1, not SW.
C7 56 pF feed-forward across the upper resistor (datasheet Eq 9 gives about 60 pF).
PG is open drain and pulled up to +3V3 through 100k (datasheet 8.3.5: pull up through a resistor; PG tolerates 20 V).
PG goes low during start-up and on a fault, so J2 pin 3 reads valid only after the 4 ms start-up delay.
D4 green fault LED from +3V3 through R_PGLED to PG: it is lit while PG is low, dark while power is good.
About 2.5 mA when lit (470 R, Vf about 2.1 V); U1's PG pull-down is about 92 ohm RDSON, so PG stays near 0.4 V.
J2 pin 1 is +3.3 V, pin 2 GND, pin 3 power-good (3.3 V logic, 100k pull-up), pin 4 GND.
D3 green power LED from the 3.3 V rail.
Two M2.5 non-plated holes in opposite corners; the board is fixed down through them.

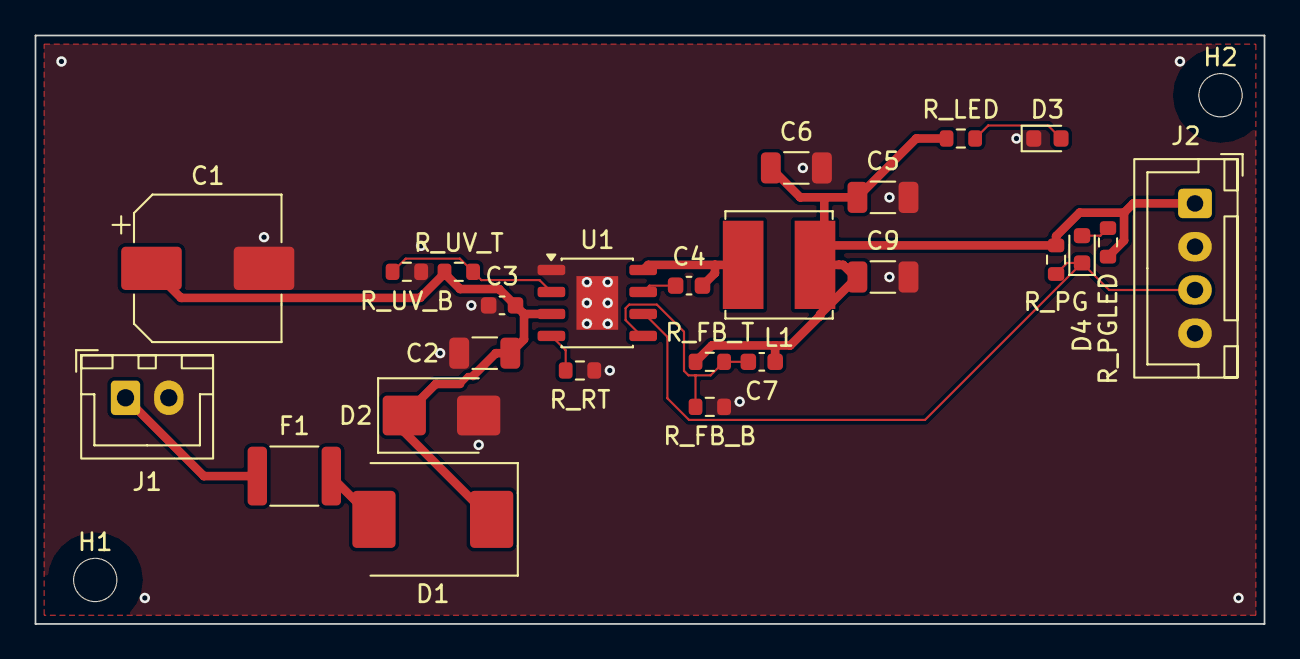
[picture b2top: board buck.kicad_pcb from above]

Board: 4 copper layers, 71.0 x 34.0 mm, 27 parts (0 on the bottom side), 13 nets.

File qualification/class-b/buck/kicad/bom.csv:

refdes,value,kind,description,kicad_symbol,kicad_footprint,lcsc_pn,mpn
C1,47uF,capacitor,"Honor Elec RVT1H470M0810, 47 uF 50 V +/-20 % 105 C SMD aluminium electrolytic, 8 mm diameter x 10.2 mm, polarised (pin 1 is +); JLCPCB C2895739",Device:C_Polarized,Capacitor_SMD:CP_Elec_8x10,,RVT1H470M0810
C2,10uF,capacitor,"Generic 1206 ceramic capacitor, any value",Device:C,Capacitor_SMD:C_1206_3216Metric,,
C3,220nF,capacitor,"Generic 0603 MLCC, X7R/X5R, any value",Device:C,Capacitor_SMD:C_0603_1608Metric,,
C4,100nF,capacitor,"Generic 0603 MLCC, X7R/X5R, any value",Device:C,Capacitor_SMD:C_0603_1608Metric,,
C5,22uF,capacitor,"Generic 1206 ceramic capacitor, any value",Device:C,Capacitor_SMD:C_1206_3216Metric,,
C6,22uF,capacitor,"Generic 1206 ceramic capacitor, any value",Device:C,Capacitor_SMD:C_1206_3216Metric,,
C7,56pF,capacitor,"Generic 0603 MLCC, X7R/X5R, any value",Device:C,Capacitor_SMD:C_0603_1608Metric,,
C9,22uF,capacitor,"Generic 1206 ceramic capacitor, any value",Device:C,Capacitor_SMD:C_1206_3216Metric,,
D1,SS36,diode,"Vishay SS36 60 V 3 A Schottky rectifier, SMC (DO-214AB), for reverse-polarity blocking",Device:D_Schottky,Diode_SMD:D_SMC,,SS36
D2,SMBJ30A,diode,"Vishay SMBJ30A 600 W unidirectional TVS, SMB (DO-214AA). max_voltage_v is the 30 V standoff VWM, not a clamp or abs max: VBR 33.3-36.8 V at 1 mA, VC 48.4 V at 12.4 A",Device:D_Zener,Diode_SMD:D_SMB,,SMBJ30A
D3,PWR,led,"Lite-On LTST-C190KGKT green AlInGaP LED, 0603, Vf 1.9 to 2.4V at 20mA",Device:LED,LED_SMD:LED_0603_1608Metric,,LTST-C190KGKT
D4,PG FAULT,led,"Lite-On LTST-C190KGKT green AlInGaP LED, 0603, Vf 1.9 to 2.4V at 20mA",Device:LED,LED_SMD:LED_0603_1608Metric,,LTST-C190KGKT
F1,1.1A_PTC,fuse,"Bourns MF-MSMF110/33X resettable PTC fuse, 1812. max_current_ma is Ihold 1.1 A at 23 C (0.63 A at 70 C, 0.50 A at 85 C); Itrip 2.2 A, Vmax 33 V",Device:Polyfuse,Fuse:Fuse_1812_4532Metric,,MF-MSMF110/33X
H1,M2.5,mounting_hole,M2.5 non-plated mounting hole (NPTH) for a board corner,Mechanical:MountingHole,MountingHole:MountingHole_2.5mm,,
H2,M2.5,mounting_hole,M2.5 non-plated mounting hole (NPTH) for a board corner,Mechanical:MountingHole,MountingHole:MountingHole_2.5mm,,
J1,24V_IN,connector,"JST XH 2.5 mm pitch 2-pin vertical header B2B-XH-A, 250 V / 3 A per JST XH sheet",Connector_Generic:Conn_01x02,Connector_JST:JST_XH_B2B-XH-A_1x02_P2.50mm_Vertical,,B2B-XH-A
J2,3V3_OUT,connector,"JST XH 2.5 mm pitch 4-pin vertical header B4B-XH-A, 250 V / 3 A per JST XH sheet",Connector_Generic:Conn_01x04,Connector_JST:JST_XH_B4B-XH-A_1x04_P2.50mm_Vertical,,B4B-XH-A
L1,6.8uH,inductor,"Bourns SRN6045TA-6R8M 6.8 uH semi-shielded power inductor, 6.0 x 6.0 mm. Datasheet typ: Isat 5.7 A (L drops 30%), Irms 3.6 A (max_current_ma is Irms), DCR 34 mOhm +-20%",Device:L,Inductor_SMD:L_Bourns_SRN6045TA,,SRN6045TA-6R8M
R_FB_B,43.2k,resistor,"Generic 0603 thick-film resistor, any value",Device:R_US,Resistor_SMD:R_0603_1608Metric,,
R_FB_T,100k,resistor,"Generic 0603 thick-film resistor, any value",Device:R_US,Resistor_SMD:R_0603_1608Metric,,
R_LED,470,resistor,"Generic 0603 thick-film resistor, any value",Device:R_US,Resistor_SMD:R_0603_1608Metric,,
R_PG,100k,resistor,"Generic 0603 thick-film resistor, any value",Device:R_US,Resistor_SMD:R_0603_1608Metric,,
R_PGLED,470,resistor,"Generic 0603 thick-film resistor, any value",Device:R_US,Resistor_SMD:R_0603_1608Metric,,
R_RT,33k,resistor,"Generic 0603 thick-film resistor, any value",Device:R_US,Resistor_SMD:R_0603_1608Metric,,
R_UV_B,100k,resistor,"Generic 0603 thick-film resistor, any value",Device:R_US,Resistor_SMD:R_0603_1608Metric,,
R_UV_T,1.37M,resistor,"Generic 0603 thick-film resistor, any value",Device:R_US,Resistor_SMD:R_0603_1608Metric,,
U1,LMR38010SDDAR,regulator,"TI LMR38010SDDAR 4.2-80 V input, 1 A synchronous step-down converter, adjustable 400 kHz-2.2 MHz through RT, PFM with spread spectrum, HSOIC-8 (DDA) with exposed thermal pad and open-drain power-good. VFB 1.0 V; VIN abs max 85 V",,Package_SO:HSOP-8-1EP_3.9x4.9mm_P1.27mm_EP2.41x3.1mm,,LMR38010SDDAR
